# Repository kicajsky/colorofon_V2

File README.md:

# colorofon_V2
3-Channel Analog Colorofon

An analog color organ based on the LM358 operational amplifier, designed to visualize an audio signal through three independent frequency channels: Low, Mid, and High.

The circuit operates from a single 12 V supply and uses a 6 V virtual ground for analog signal processing. Each frequency channel independently processes the audio signal and provides a dedicated output for controlling external lighting.

3 frequency channels: Low / Mid / High
Fully analog signal processing
MCP6002 operational amplifier
12 V single-supply operation
6 V virtual ground
Audio signal input
Independent output for each channel
Schematic, PCB design, board view included

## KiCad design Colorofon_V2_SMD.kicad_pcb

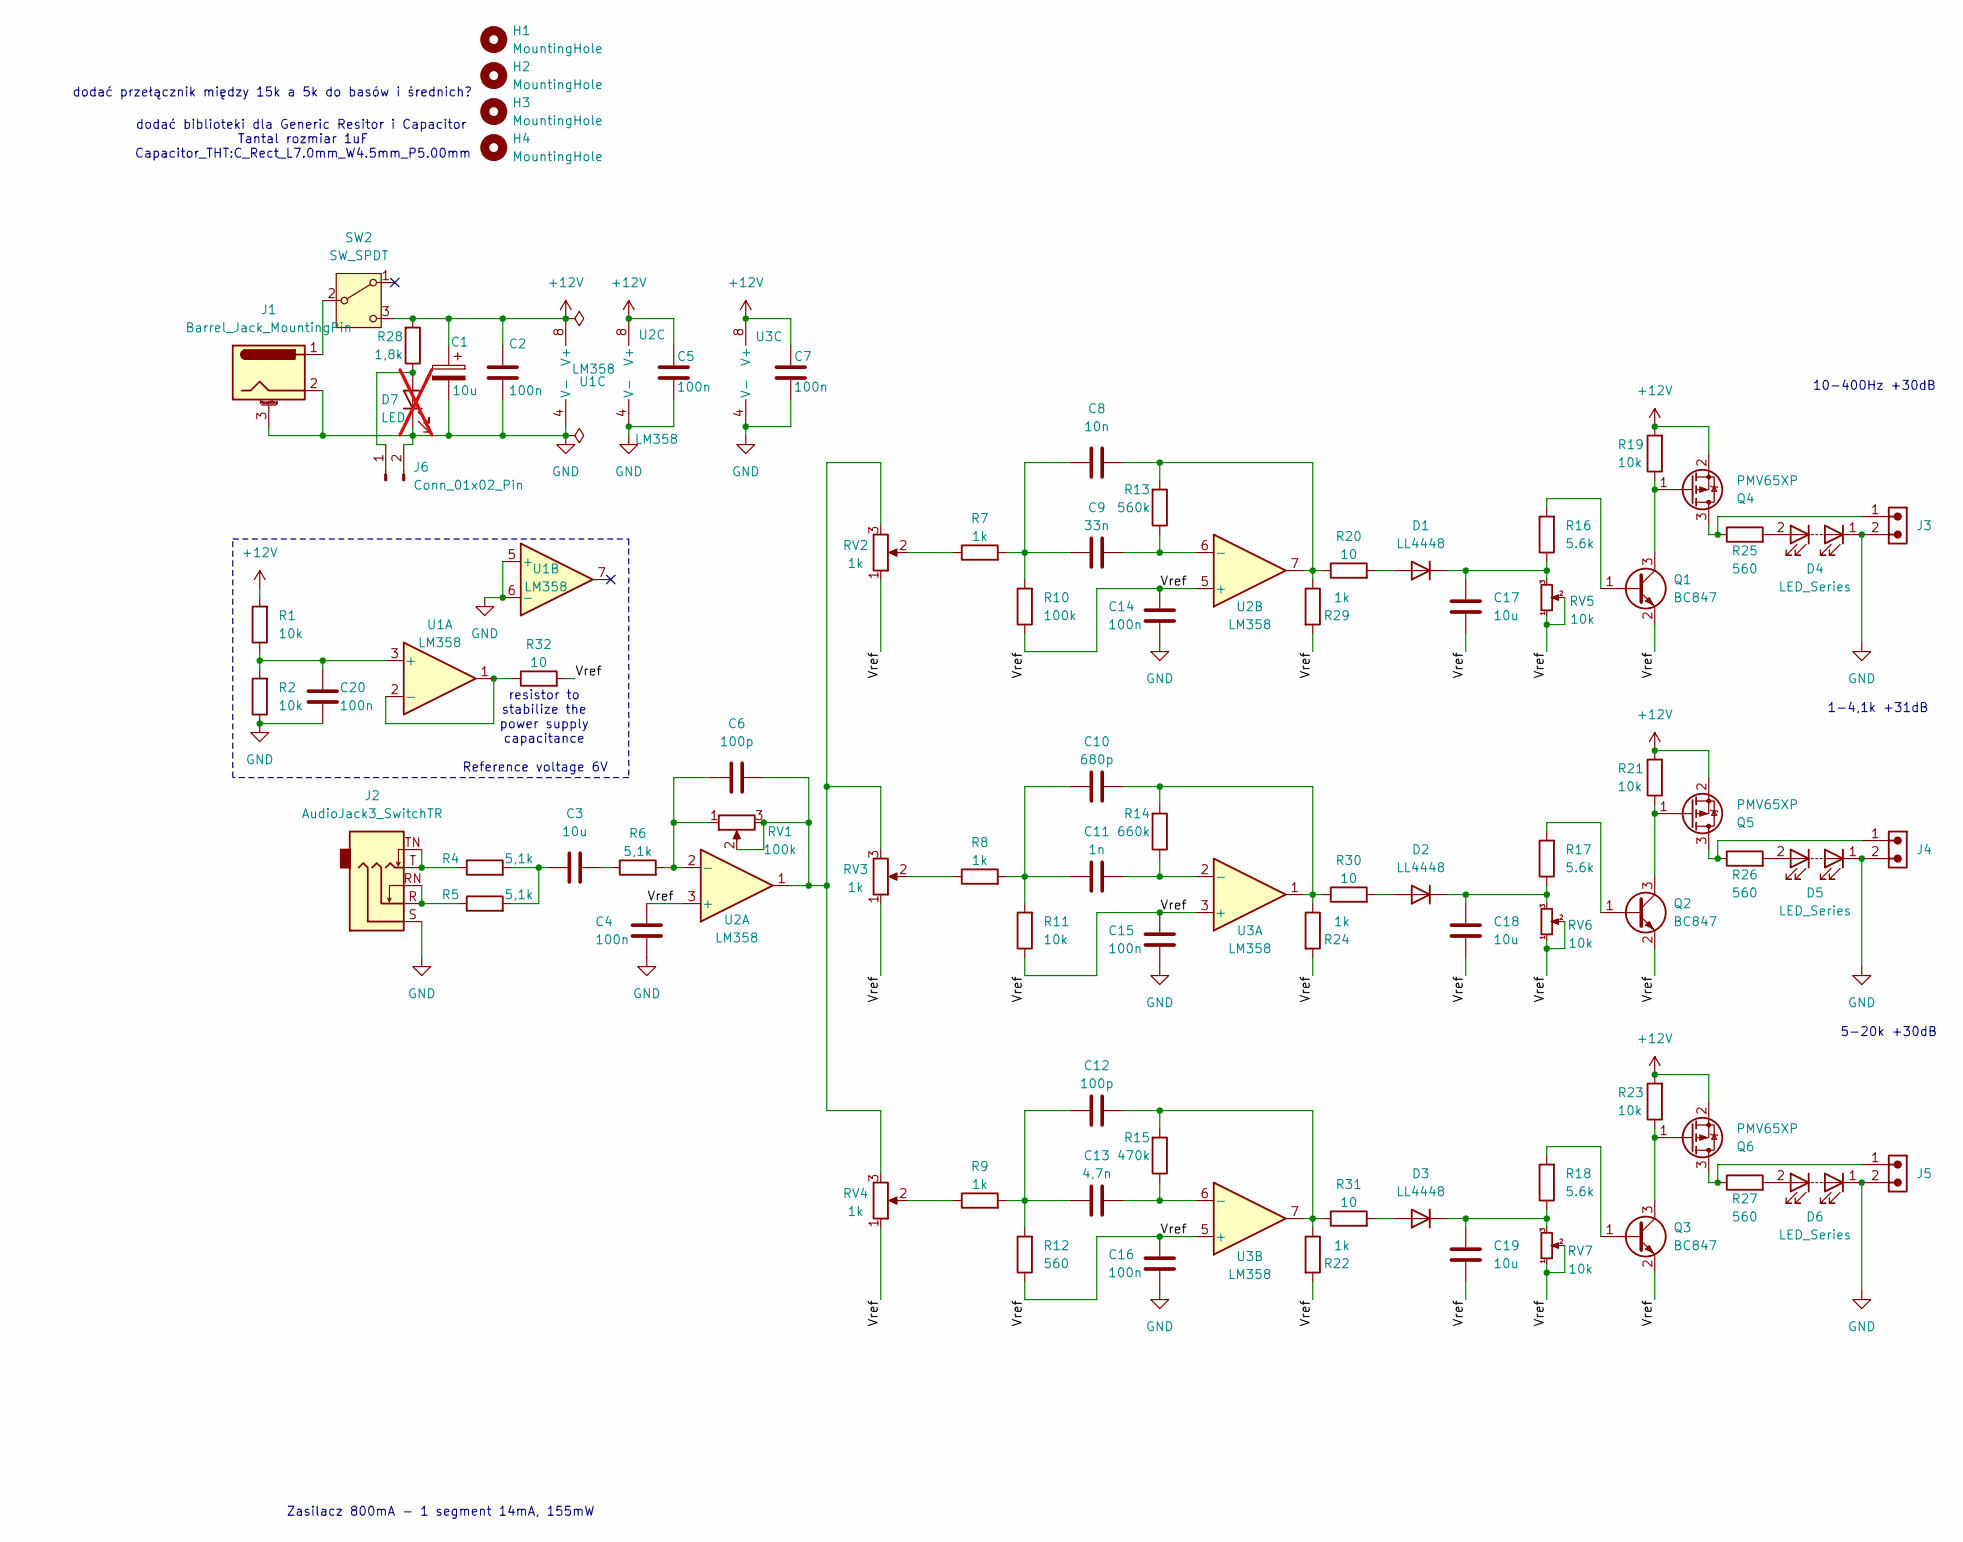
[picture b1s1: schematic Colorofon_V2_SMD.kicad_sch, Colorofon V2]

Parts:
C1, C3, C17, C18, C19: 10u; C_1206_3216Metric_Pad1.33x1.80mm_HandSolder
C2, C4, C5, C7, C14, C15, C16, C20: 100n; C_0805_2012Metric_Pad1.18x1.45mm_HandSolder
C6, C12: 100p; C_1206_3216Metric_Pad1.33x1.80mm_HandSolder
C8: 10n; C_1206_3216Metric_Pad1.33x1.80mm_HandSolder
C9: 33n; C_1206_3216Metric_Pad1.33x1.80mm_HandSolder
C10: 680p; C_1206_3216Metric_Pad1.33x1.80mm_HandSolder
C11: 1n; C_1206_3216Metric_Pad1.33x1.80mm_HandSolder
C13: 4,7n; C_1206_3216Metric_Pad1.33x1.80mm_HandSolder
D1, D2, D3: LL4448; D_MiniMELF
D4, D5, D6: LED_Series; LED_1206_3216Metric_Pad1.42x1.75mm_HandSolder
D7: LED; not fitted
H1, H2, H3, H4: MountingHole; MountingHole_2.2mm_M2
J1: Barrel_Jack_MountingPin; BarrelJack_Horizontal
J2: AudioJack3_SwitchTR; Jack_3.5mm_CUI_SJ2-3593D-SMT_Horizontal
J3, J4, J5: Connector 1x2 WE 691322310002; J_Wurth_WR-TBL_691322310002; Part Number 691322310002
J6: Conn_01x02_Pin; PinHeader_1x02_P2.54mm_Vertical_Hand_Solder
Q1, Q2, Q3: BC847; SOT-23
Q4, Q5, Q6: PMV65XP; SOT-23
R1, R2, R11, R19, R21, R23: 10k; R_1206_3216Metric_Pad1.30x1.75mm_HandSolder
R4, R5, R6: 5,1k; R_1206_3216Metric_Pad1.30x1.75mm_HandSolder
R7, R8, R9, R22, R24, R29: 1k; R_1206_3216Metric_Pad1.30x1.75mm_HandSolder
R10: 100k; R_1206_3216Metric_Pad1.30x1.75mm_HandSolder
R12, R25, R26, R27: 560; R_1206_3216Metric_Pad1.30x1.75mm_HandSolder
R13: 560k; R_1206_3216Metric_Pad1.30x1.75mm_HandSolder
R14: 660k; R_1206_3216Metric_Pad1.30x1.75mm_HandSolder
R15: 470k; R_1206_3216Metric_Pad1.30x1.75mm_HandSolder
R16, R17, R18: 5.6k; R_1206_3216Metric_Pad1.30x1.75mm_HandSolder
R20, R30, R31, R32: 10; R_1206_3216Metric_Pad1.30x1.75mm_HandSolder
R28: 1,8k; R_1206_3216Metric_Pad1.30x1.75mm_HandSolder
RV1: 100k; Potentiometer_Piher_T-16H_Single_Horizontal
RV2, RV3, RV4: 1k; Potentiometer_Piher_T-16H_Single_Horizontal
RV5, RV6, RV7: 10k; Potentiometer_Runtron_RM-065_Vertical_Hand_Solder
SW2: SW_SPDT; SW_Toggle_Blue_wSlots
U1, U2, U3: LM358; DIP-8_W7.62mm_Socket_LongPads

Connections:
+12V: C1.1, C2.2, C5.2, C7.2, Q4.2 (S), Q5.2 (S), Q6.2 (S), R1.2, R19.2, R21.2, R23.2, R28.2, SW2.3 (C), U1.8 (V+), U2.8 (V+), U3.8 (V+)
/Vref: C4.2, C14.2, C15.2, C16.2, C17.1, C18.1, C19.1, Q1.2 (E), Q2.2 (E), Q3.2 (E), R10.1, R11.1, R12.1, R22.2, R24.2, R29.2, R32.2, RV2.1, RV3.1, RV4.1, RV5.1, RV5.2, RV6.1, RV6.2, RV7.1, RV7.2, U2.3 (+), U2.5 (+), U3.3 (+), U3.5 (+)
GND: C1.2, C2.1, C4.1, C5.1, C7.1, C14.1, C15.1, C16.1, C20.1, D4.1 (K), D5.1 (K), D6.1 (K), D7.1 (K), J1.2, J1.3 (MountPin_3), J2.S, J3.2, J4.2, J5.2, J6.2, R2.1, U1.4 (V-), U1.5 (+), U1.6 (-), U2.4 (V-), U3.4 (V-)
unnamed: C3.1, R4.2, R5.2
unnamed: C3.2, R6.1
unnamed: C6.2, RV1.2, RV1.3, RV2.3, RV3.3, RV4.3, U2.1
unnamed: C8.1, R13.2, R20.1, R29.1, U2.7
unnamed: C8.2, C9.2, R7.2, R10.2
unnamed: C10.1, R14.2, R24.1, R30.1, U3.1
unnamed: C10.2, C11.2, R8.2, R11.2
unnamed: C12.1, R15.2, R22.1, R31.1, U3.7
unnamed: C12.2, C13.2, R9.2, R12.2
unnamed: D1.2 (A), R20.2
unnamed: C17.2, D1.1 (K), R16.1, RV5.3
unnamed: D2.2 (A), R30.2
unnamed: C18.2, D2.1 (K), R17.1, RV6.3
unnamed: D3.2 (A), R31.2
unnamed: C19.2, D3.1 (K), R18.1, RV7.3
unnamed: D4.2 (A), R25.2
unnamed: D5.2 (A), R26.2
unnamed: D6.2 (A), R27.2
unnamed: J2.R, J2.RN, R5.1
unnamed: J2.T, J2.TN, R4.1
unnamed: D7.2 (A), J6.1, R28.1
unnamed: Q1.1 (B), R16.2
unnamed: Q1.3 (C), Q4.1 (G), R19.1
unnamed: Q2.1 (B), R17.2
unnamed: Q2.3 (C), Q5.1 (G), R21.1
unnamed: Q3.1 (B), R18.2
unnamed: Q3.3 (C), Q6.1 (G), R23.1
unnamed: J3.1, Q4.3 (D), R25.1
unnamed: J4.1, Q5.3 (D), R26.1
unnamed: J5.1, Q6.3 (D), R27.1
unnamed: R7.1, RV2.2
unnamed: R8.1, RV3.2
unnamed: R9.1, RV4.2
unnamed: J1.1, SW2.2 (B)
unnamed: C20.2, R1.1, R2.2, U1.3 (+)
unnamed: R32.1, U1.1, U1.2 (-)
unnamed: C6.1, R6.2, RV1.1, U2.2 (-)
unnamed: C9.1, R13.1, U2.6 (-)
unnamed: C11.1, R14.1, U3.2 (-)
unnamed: C13.1, R15.1, U3.6 (-)

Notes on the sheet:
1-4,1k +31dB
10-400Hz +30dB
dodać przełącznik między 15k a 5k do basów i średnich?
Reference voltage 6V
Tantal rozmiar 1uF Capacitor_THT:C_Rect_L7.0mm_W4.5mm_P5.00mm
Zasilacz 800mA - 1 segment 14mA, 155mW
resistor to stabilize the power supply capacitance
5-20k +30dB
dodać biblioteki dla Generic Resitor i Capacitor

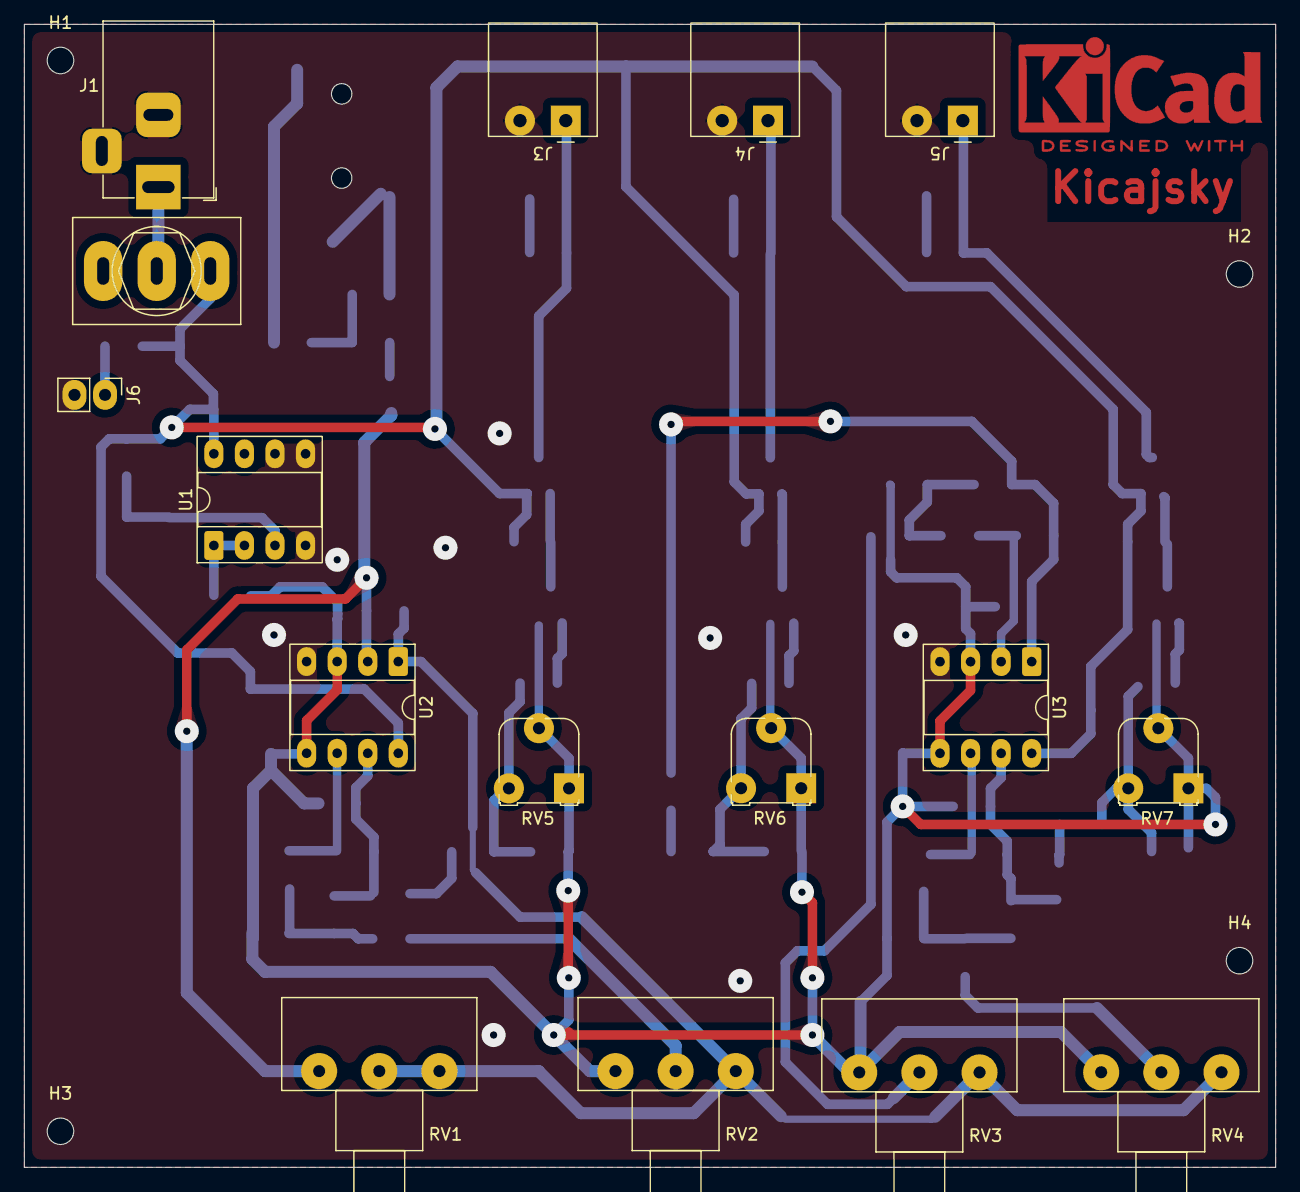
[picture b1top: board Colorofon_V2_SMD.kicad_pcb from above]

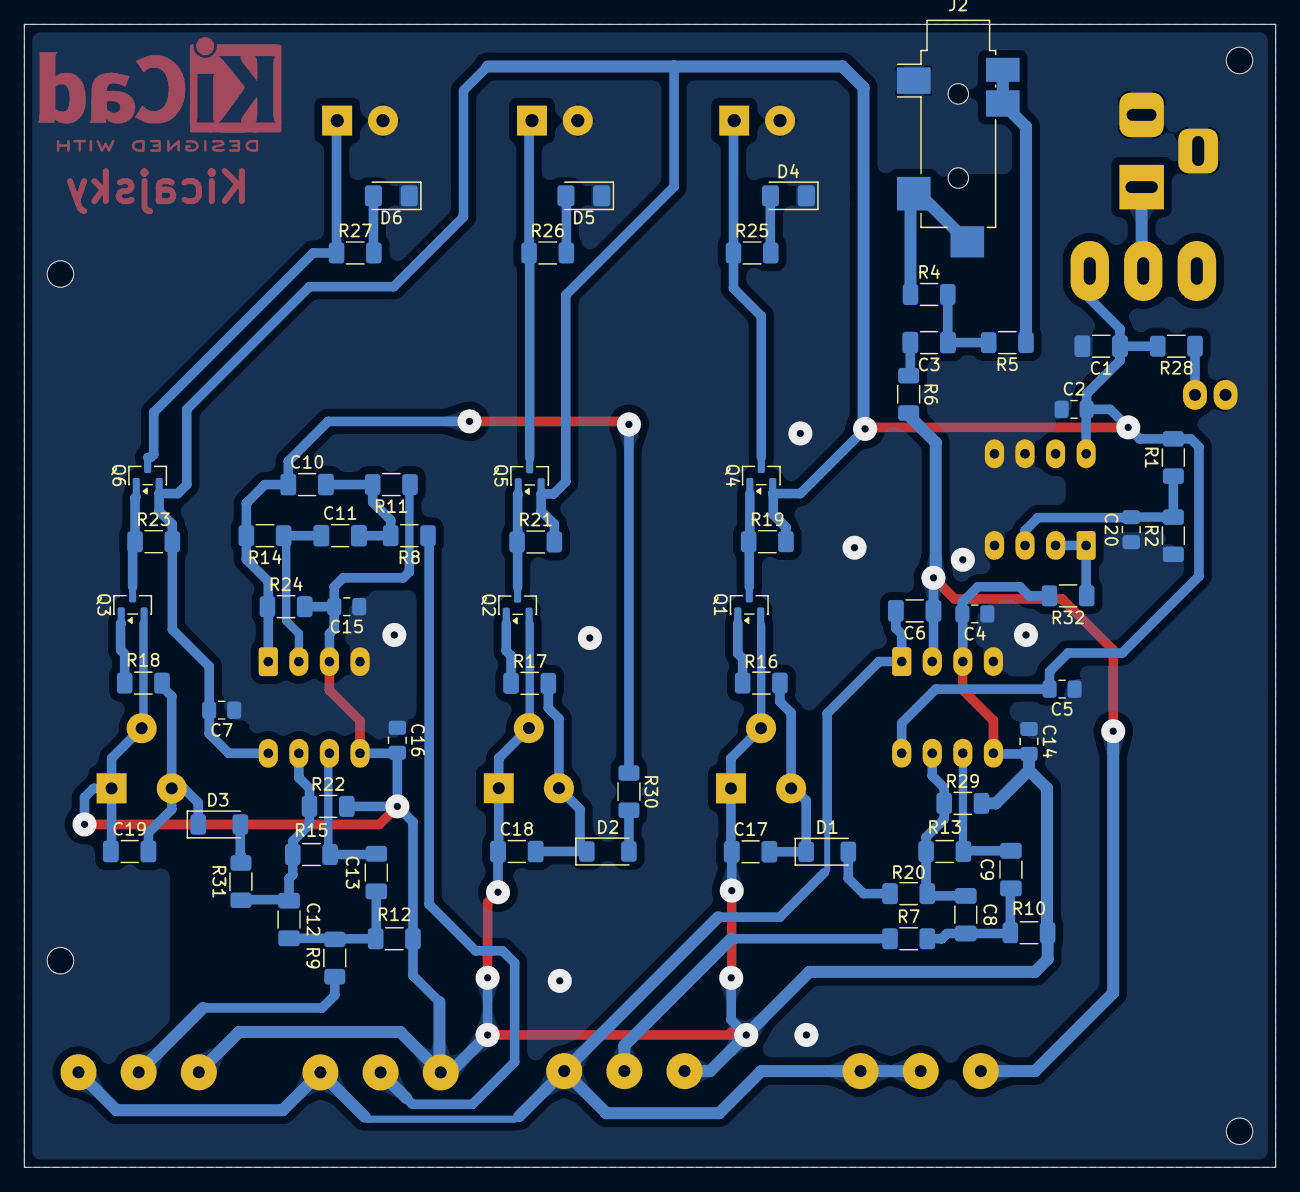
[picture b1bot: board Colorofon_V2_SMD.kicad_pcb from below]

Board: 2 copper layers, 104.0 x 95.0 mm, 84 parts (64 on the bottom side), 43 nets.

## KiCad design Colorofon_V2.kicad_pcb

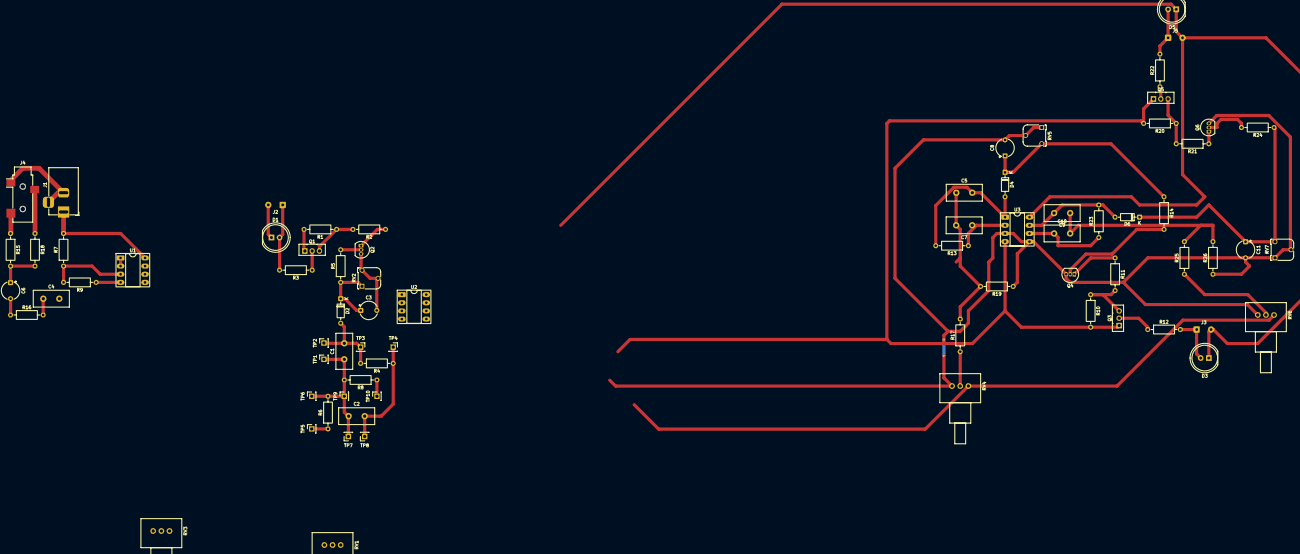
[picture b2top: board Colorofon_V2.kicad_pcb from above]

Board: 2 copper layers, 74 parts (0 on the bottom side), 40 nets.

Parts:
C1, C2: 18n; C_Disc_D11.0mm_W5.0mm_P5.00mm
C3, C8, C11: 4.7u; CP_Radial_Tantal_D5.5mm_P5.00mm
C4: 100p; C_Disc_D11.0mm_W5.0mm_P5.00mm
C5, C7, C9, C10: 47n; C_Disc_D11.0mm_W5.0mm_P5.00mm
C6: 10u; CP_Radial_Tantal_D5.5mm_P5.00mm
D1, D3, D5: LED_Series; LED_D8.0mm
D2, D4, D6: 1N4148; D_DO-35_SOD27_P7.62mm_Horizontal
J1: Barrel_Jack_MountingPin; BarrelJack_Horizontal
J2, J3, J5: Conn_01x02_Socket; SolderWire-0.25sqmm_1x02_P4.5mm_D0.65mm_OD2mm
J4: AudioJack3; Jack_3.5mm_CUI_SJ-3523-SMT_Horizontal
Q1, Q3, Q5: BD140; TO-126-3_Vertical
Q2, Q4, Q6: BC547; TO-92_Inline
R1, R7, R8, R9, R10, R19, R20, R26: 10k; R_Axial_DIN0207_L6.3mm_D2.5mm_P10.16mm_Horizontal
R2, R11, R21: 100; R_Axial_DIN0207_L6.3mm_D2.5mm_P10.16mm_Horizontal
R3, R12, R22: 560; R_Axial_DIN0207_L6.3mm_D2.5mm_P10.16mm_Horizontal
R4: 351k; R_Axial_DIN0207_L6.3mm_D2.5mm_P10.16mm_Horizontal
R5, R14, R17, R24, R25: 5.6k; R_Axial_DIN0207_L6.3mm_D2.5mm_P10.16mm_Horizontal
R6: 88k; R_Axial_DIN0207_L6.3mm_D2.5mm_P10.16mm_Horizontal
R13, R23: 330k; R_Axial_DIN0207_L6.3mm_D2.5mm_P10.16mm_Horizontal
R15, R16, R18: 5.1k; R_Axial_DIN0207_L6.3mm_D2.5mm_P10.16mm_Horizontal
RV1, RV3, RV4, RV6: 100k; Potentiometer_Vishay_148-149_Single_Horizontal
RV2, RV5, RV7: 10k; Potentiometer_Runtron_RM-065_Vertical
TP1, TP2, TP3, TP4, TP5, TP6, TP7, TP8, TP9, TP10: TestPoint_Alt; PinSocket_1x01_P2.54mm_Vertical
U1: LM358; DIP-8_W7.62mm_Socket_LongPads
U2, U3: MCP6002-xP; DIP-8_W7.62mm_Socket_LongPads

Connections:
+12V: J1.1, Q1.1 (E), Q3.1 (E), Q5.1 (E), R1.2, R7.2, R10.2, R20.2, U1.8 (V+), U2.4 (V-), U3.4 (V-)
/Vref: C3.2, C8.2, C11.2, Q2.3 (E), Q4.3 (E), Q6.3 (E), R8.1, R19.1, R26.1, RV1.1, RV2.1, RV2.2, RV4.1, RV5.1, RV5.2, RV6.1, RV7.1, RV7.2, TP10.1 (1_1), U1.1, U1.2 (-), U2.3 (+), U2.5 (+), U3.3 (+), U3.5 (+)
GND: D1.1 (K), D3.1 (K), D5.1 (K), J1.2, J1.MP (MountPin_MP), J2.2, J3.2, J4.S, J5.2, R9.1, U1.4 (V-), U2.8 (V+), U3.8 (V+)
unnamed: C1.1, C2.2, R6.2, R8.2, TP1.1 (1_1), TP6.1 (1_1), TP7.1 (1_1), TP9.1 (1_1)
unnamed: C4.2, RV1.3, RV3.1, RV3.2, RV4.3, RV6.3, U2.1
unnamed: C5.1, C7.2, R17.2, R19.2
unnamed: C6.1, R15.2, R18.2
unnamed: C6.2, R16.1
unnamed: C9.1, C10.2, R25.2, R26.2
unnamed: D1.2 (A), J2.1, R3.2
unnamed: C1.2, D2.2 (A), R4.2, TP2.1 (1_1), TP3.1 (1_1), U2.7
unnamed: C3.1, D2.1 (K), R5.1, RV2.3
unnamed: D3.2 (A), J3.1, R12.2
unnamed: C5.2, D4.2 (A), R13.2, U3.1
unnamed: C8.1, D4.1 (K), R14.1, RV5.3
unnamed: D5.2 (A), J5.1, R22.2
unnamed: C9.2, D6.2 (A), R23.2, U3.7
unnamed: C11.1, D6.1 (K), R24.1, RV7.3
unnamed: J4.R, R18.1
unnamed: J4.T, R15.1
unnamed: Q1.3 (B), R1.1, R2.2
unnamed: Q1.2 (C), R3.1
unnamed: Q2.2 (B), R5.2
unnamed: Q2.1 (C), R2.1
unnamed: Q3.3 (B), R10.1, R11.2
unnamed: Q3.2 (C), R12.1
unnamed: Q4.2 (B), R14.2
unnamed: Q4.1 (C), R11.1
unnamed: Q5.3 (B), R20.1, R21.2
unnamed: Q5.2 (C), R22.1
unnamed: Q6.2 (B), R24.2
unnamed: Q6.1 (C), R21.1
unnamed: R6.1, RV1.2, TP5.1 (1_1)
unnamed: R17.1, RV4.2
unnamed: R25.1, RV6.2
unnamed: R7.1, R9.2, U1.3 (+)
unnamed: C4.1, R16.2, RV3.3, U2.2 (-)
unnamed: C2.1, R4.1, TP4.1 (1_1), TP8.1 (1_1), U2.6 (-)
unnamed: C7.1, R13.1, U3.2 (-)
unnamed: C10.1, R23.1, U3.6 (-)
